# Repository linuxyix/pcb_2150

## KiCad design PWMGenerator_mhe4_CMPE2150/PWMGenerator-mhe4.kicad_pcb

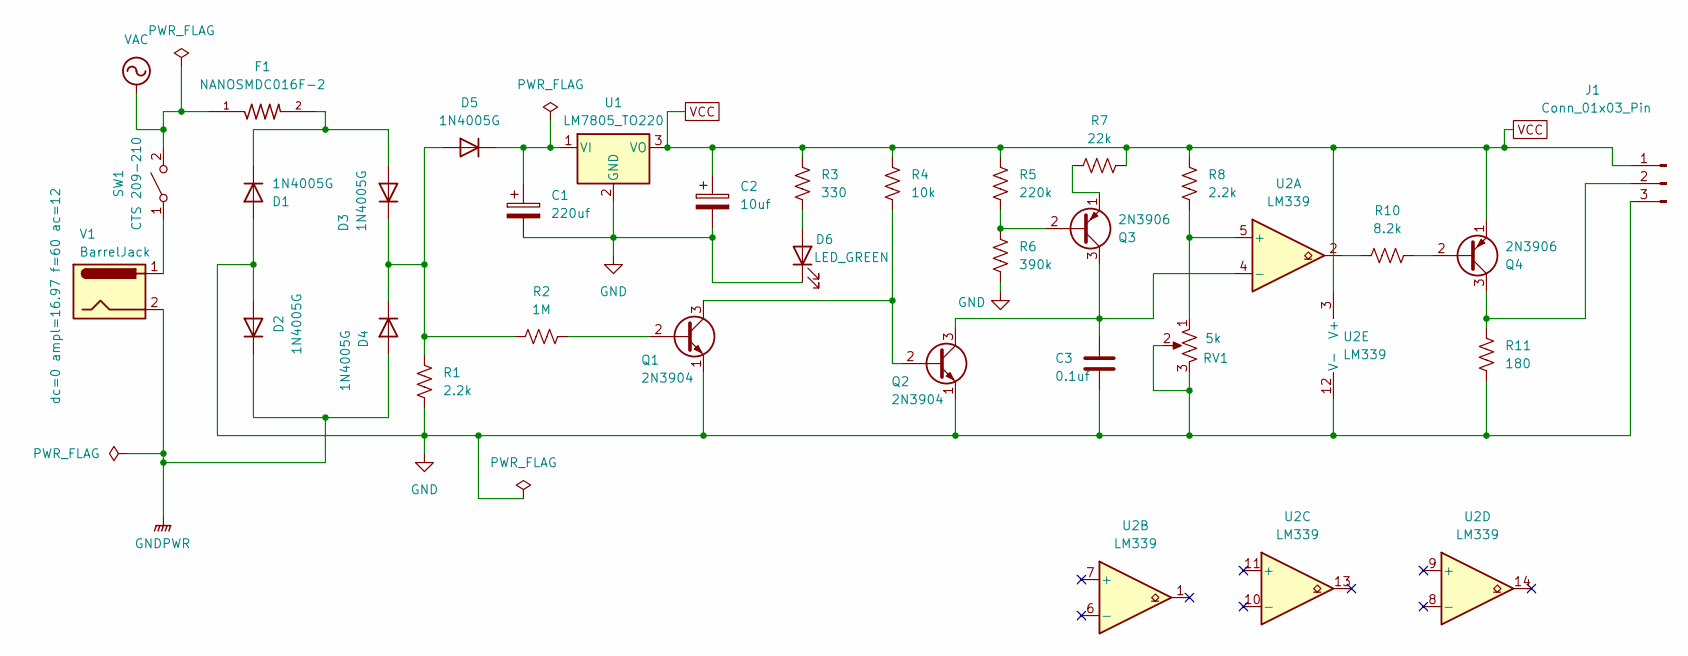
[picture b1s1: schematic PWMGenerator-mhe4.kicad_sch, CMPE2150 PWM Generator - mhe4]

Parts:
C1: 220uf; CP_Radial_D8.0mm_P3.50mm
C2: 10uf; CP_Radial_D4.0mm_P1.50mm
C3: 0.1uf; C_0805_2012Metric
D1, D2, D3, D4, D5: 1N4005G; D_0805_2012Metric
D6: LED_GREEN; LED_D5.0mm
F1: NANOSMDC016F-2; RESC3115X65N
J1: Conn_01x03_Pin; PinHeader_1x03_P2.54mm_Vertical
Q1, Q2: 2N3904; SOT-23
Q3, Q4: 2N3906; SOT-23
R1, R8: 2.2k; R_0805_2012Metric
R2: 1M; R_0805_2012Metric
R3: 330; R_0805_2012Metric
R4: 10k; R_0805_2012Metric
R5: 220k; R_0805_2012Metric
R6: 390k; R_0805_2012Metric
R7: 22k; R_0805_2012Metric
R10: 8.2k; R_0805_2012Metric
R11: 180; R_0805_2012Metric
RV1: 5k; Potentiometer_Alps_RK09K_Single_Vertical
SW1: CTS 209-210; SW_DIP_SPSTx01_Slide_6.7x4.1mm_W7.62mm_P2.54mm_LowProfile
U1: LM7805_TO220; TO-220-3_Vertical
U2: LM339; SOIC-14_3.9x8.7mm_P1.27mm
V1: BarrelJack; BarrelJack_SwitchcraftConxall_RAPC10U_Horizontal

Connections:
GND: C1.2, C2.2, C3.2, D1.2 (A), D2.2 (A), D6.1 (K), J1.3, Q1.1 (E), Q2.1 (E), R1.2, R6.2, R11.2, RV1.2, RV1.3, U1.2 (GND), U2.12 (V-)
GNDPWR: D2.1 (K), D4.2 (A), V1.2
unnamed: D1.1 (K), D3.2 (A), F1.2
unnamed: D3.1 (K), D4.1 (K), D5.2 (A), R1.1, R2.1
unnamed: C1.1, D5.1 (K), U1.1 (VI)
unnamed: D6.2 (A), R3.2
unnamed: J1.2, Q4.3 (C), R11.1
unnamed: Q1.2 (B), R2.2
unnamed: Q1.3 (C), Q2.2 (B), R4.2
unnamed: C3.1, Q2.3 (C), Q3.3 (C), U2.4 (-)
unnamed: Q3.2 (B), R5.2, R6.1
unnamed: Q3.1 (E), R7.1
unnamed: Q4.2 (B), R10.2
unnamed: R10.1, U2.2
unnamed: SW1.1 (A), V1.1
unnamed: R8.2, RV1.1, U2.5 (+)
VAC: F1.1, SW1.2 (B)
VCC: C2.1, J1.1, Q4.1 (E), R3.1, R4.1, R5.1, R7.2, R8.1, U1.3 (VO), U2.3 (V+)

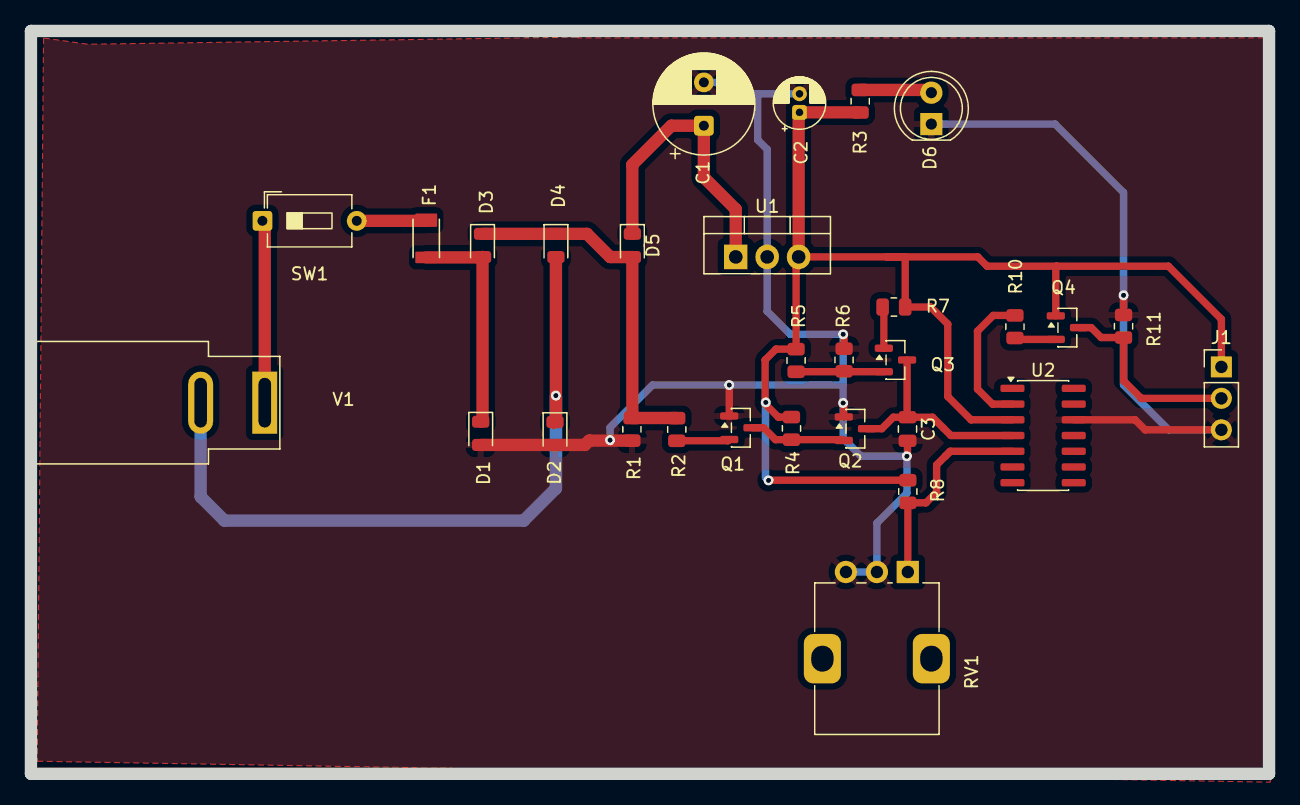
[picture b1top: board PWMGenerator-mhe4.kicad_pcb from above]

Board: 2 copper layers, 100.0 x 60.0 mm, 30 parts (0 on the bottom side), 18 nets.

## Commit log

2025-12-11 programCreation
    1
2025-12-11 add component
    1
2025-12-12 us symbal rev
    1
2025-12-12 all error fixed
    1
2025-12-12 partB still working
    1
2025-12-13 partB done(no error)
    1
2025-12-13 setting update
    1
2025-12-13 pcb Board setting update
    1
2025-12-13 final schematic check(no error)
    1
2025-12-13 rev:3 shcematic_confirmation
    this schematic will be used for pbc component placement
2025-12-13 fix: connected U1 pin3 to VCC
    1
2025-12-13 fix: potentiometer
    1
2025-12-13 ProjC_import success
    1
2025-12-16 partc component placement
    1
2025-12-16 parct c cu
    update
2025-12-16 cu/connect update
    1
2025-12-16 F.cu B.cu update
    1
